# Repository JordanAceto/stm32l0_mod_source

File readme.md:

## Small STM32L0 based modulation source PCB

### Features:
- tiny pcb
- four analog inputs
- three digital input/outputs
- two analog outputs
- it can be configured for various modulation duties, such as
    - a dual LFO
    - a single ADSR
    - other things?
- drop it into various projects that need a small modulation source

### Status:

Task | Status |
---------|--------------|
Schematic capture | &#9745;
PCB layout | &#9745;
Test build | &#9745;
Safe to order boards| &#9745;

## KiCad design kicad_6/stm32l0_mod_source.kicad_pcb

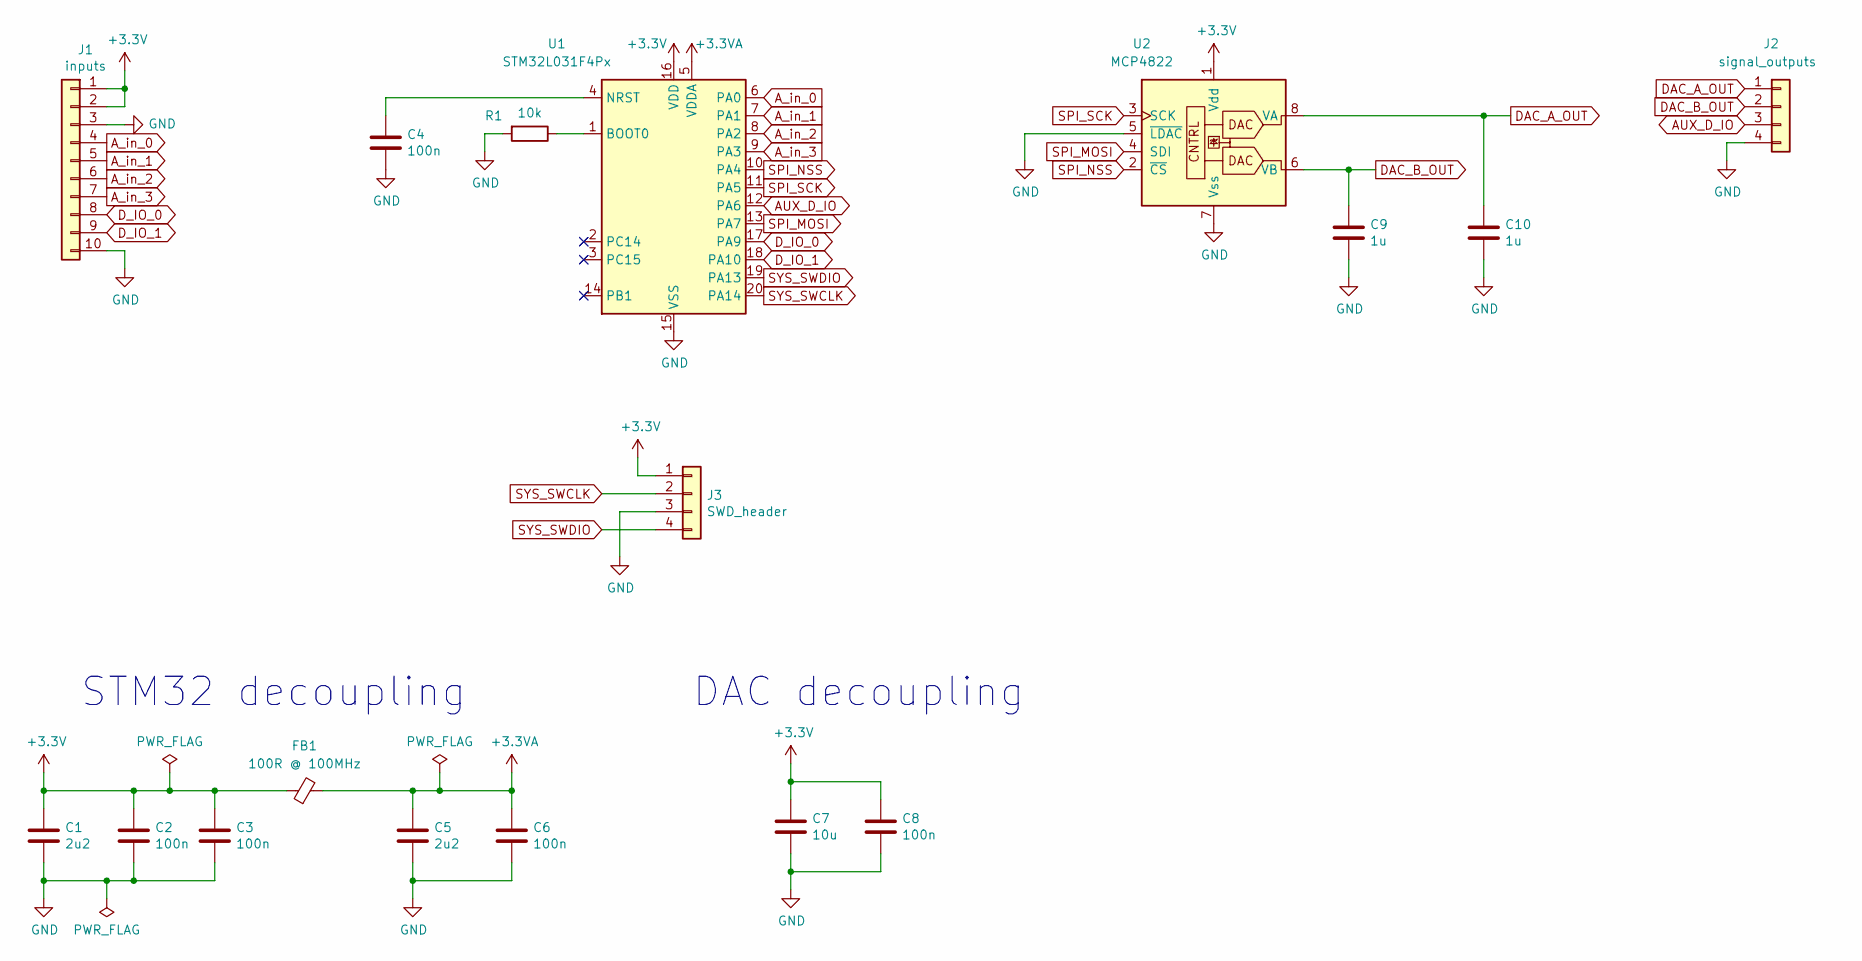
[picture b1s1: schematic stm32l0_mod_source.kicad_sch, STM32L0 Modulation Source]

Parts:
C1, C5: 2u2; C_0805_2012Metric
C2, C3, C4, C6, C8: 100n; C_0603_1608Metric
C7: 10u; C_0805_2012Metric
C9, C10: 1u; C_0805_2012Metric
FB1: 100R @ 100MHz; L_0805_2012Metric
J1: inputs; PinHeader_1x10_P2.54mm_Vertical
J2: signal_outputs; PinHeader_1x04_P2.54mm_Vertical
J3: SWD_header; PinHeader_1x04_P2.54mm_Vertical
R1: 10k; R_0603_1608Metric
U1: STM32L031F4Px; TSSOP-20_4.4x6.5mm_P0.65mm
U2: MCP4822; MSOP-8_3x3mm_P0.65mm

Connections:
+3.3V: C1.1, C2.1, C3.1, C7.1, C8.1, FB1.1, J1.1, J1.2, J3.1, U1.16 (VDD), U2.1 (Vdd)
+3.3VA: C5.1, C6.1, FB1.2, U1.5 (VDDA)
AUX_D_IO: J2.3, U1.12 (PA6)
A_in_0: J1.4, U1.6 (PA0)
A_in_1: J1.5, U1.7 (PA1)
A_in_2: J1.6, U1.8 (PA2)
A_in_3: J1.7, U1.9 (PA3)
DAC_A_OUT: C10.1, J2.1, U2.8 (VA)
DAC_B_OUT: C9.1, J2.2, U2.6 (VB)
D_IO_0: J1.8, U1.17 (PA9)
D_IO_1: J1.9, U1.18 (PA10)
GND: C1.2, C2.2, C3.2, C4.2, C5.2, C6.2, C7.2, C8.2, C9.2, C10.2, J1.3, J1.10, J2.4, J3.3, R1.2, U1.15 (VSS), U2.5 (~LDAC), U2.7 (Vss)
unnamed: C4.1, U1.4 (NRST)
unnamed: R1.1, U1.1 (BOOT0)
SPI_MOSI: U1.13 (PA7), U2.4 (SDI)
SPI_NSS: U1.10 (PA4), U2.2 (~CS)
SPI_SCK: U1.11 (PA5), U2.3 (SCK)
SYS_SWCLK: J3.2, U1.20 (PA14)
SYS_SWDIO: J3.4, U1.19 (PA13)

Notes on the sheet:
STM32 decoupling
DAC decoupling

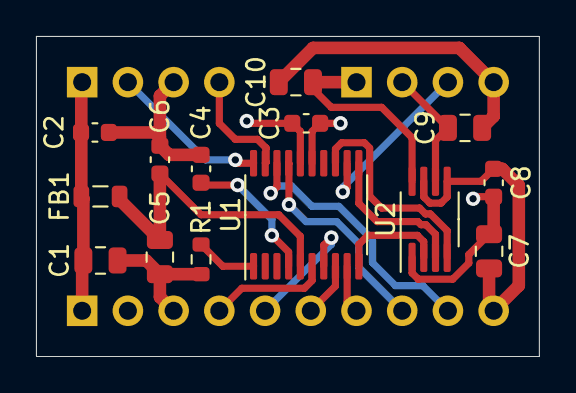
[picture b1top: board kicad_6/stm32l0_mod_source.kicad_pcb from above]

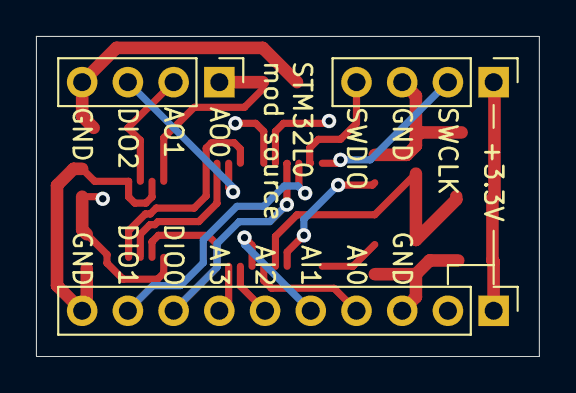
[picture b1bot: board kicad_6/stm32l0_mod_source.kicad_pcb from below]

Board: 4 copper layers, 27.9 x 17.8 mm, 17 parts (3 on the bottom side), 19 nets.

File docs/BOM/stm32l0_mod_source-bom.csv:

Row,Description,Part,References,Value,Footprint,Quantity Per PCB,Status,Datasheet
1,Unpolarized capacitor,C,C2 C3 C4 C6 C8,100n,C_0603_1608Metric,5, ,~
2,Unpolarized capacitor,C,C9 C10,1u,C_0805_2012Metric,2, ,~
3,Unpolarized capacitor,C,C1 C5,2u2,C_0805_2012Metric,2, ,~
4,Unpolarized capacitor,C,C7,10u,C_0805_2012Metric,1, ,~
5,"Ferrite bead, small symbol",FerriteBead_Small,FB1,100R @ 100MHz,L_0805_2012Metric,1, ,~
6,"Generic connector, single row, 01x10, script generated (kicad-library-utils/schlib/autogen/connector/)",Conn_01x10,J1,inputs,PinHeader_1x10_P2.54mm_Vertical,1, ,~
7,"Generic connector, single row, 01x04, script generated (kicad-library-utils/schlib/autogen/connector/)",Conn_01x04,J2 J3,signal_outputs,PinHeader_1x04_P2.54mm_Vertical,2, ,~
8,Resistor,R,R1,10k,R_0603_1608Metric,1, ,~
9,2-Channel 12-Bit D/A Converters with SPI Interface and Internal Reference (2.048V),MCP4822,U2,MCP4822,MSOP-8_3x3mm_P0.65mm,1, ,http://ww1.microchip.com/downloads/en/DeviceDoc/20002249B.pdf
10,"ARM Cortex-M0+ MCU, 16KB flash, 8KB RAM, 32MHz, 1.65-3.6V, 15 GPIO, TSSOP-20",STM32L031F4Px,U1,STM32L031F4Px,TSSOP-20_4.4x6.5mm_P0.65mm,1, ,http://www.st.com/st-web-ui/static/active/en/resource/techni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





Project info:
Schematic:,stm32l0_mod_source
Variant:,default
Revision:,0.1
Date:,2022-01-15
KiCad Version:,6.0.5+dfsg-1~bpo11+1
Statistics:
Component Groups:,10
Component Count:,17 (14 SMD/ 3 THT)
Fitted Components:,17 (14 SMD/ 3 THT)
Number of PCBs:,1
Total Components:,17

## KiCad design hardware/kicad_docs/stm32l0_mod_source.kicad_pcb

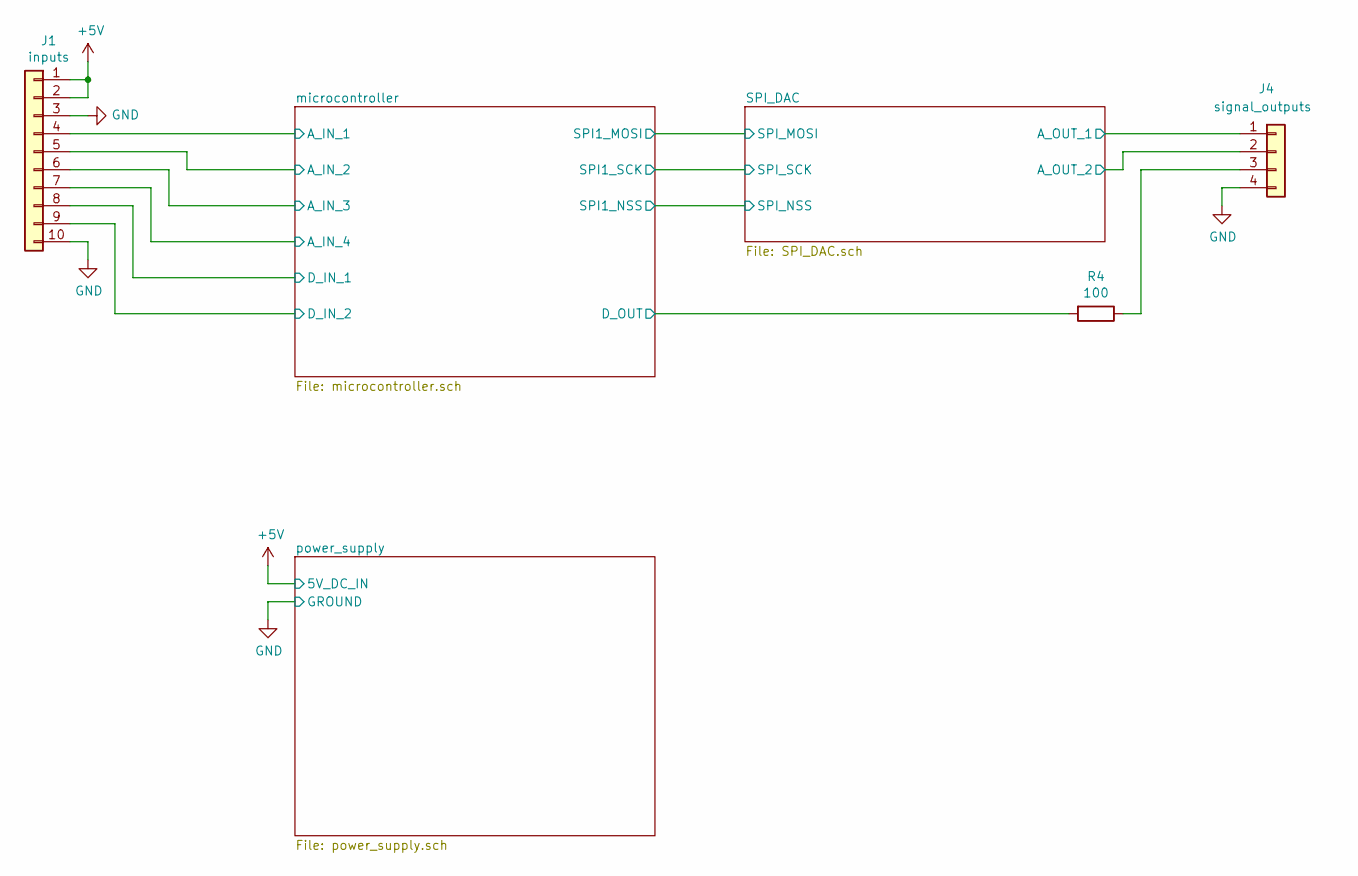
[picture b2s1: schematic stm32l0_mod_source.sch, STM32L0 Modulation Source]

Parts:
J1: inputs; PinHeader_1x10_P2.54mm_Vertical
J4: signal_outputs; PinHeader_1x04_P2.54mm_Vertical
R4: 100; R_0603_1608Metric

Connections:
+5V: J1.1, J1.2; also elsewhere on the board
/SPI_DAC_and_lowpass_filters/A_OUT_1: J4.1; also elsewhere on the board
/SPI_DAC_and_lowpass_filters/A_OUT_2: J4.2; also elsewhere on the board
/microcontroller/A_IN_1: J1.4; also elsewhere on the board
/microcontroller/A_IN_2: J1.5; also elsewhere on the board
/microcontroller/A_IN_3: J1.6; also elsewhere on the board
/microcontroller/A_IN_4: J1.7; also elsewhere on the board
/microcontroller/D_IN_1: J1.8; also elsewhere on the board
/microcontroller/D_IN_2: J1.9; also elsewhere on the board
/microcontroller/D_OUT: R4.2; also elsewhere on the board
GND: J1.3, J1.10, J4.4; also elsewhere on the board
unnamed: J4.3, R4.1

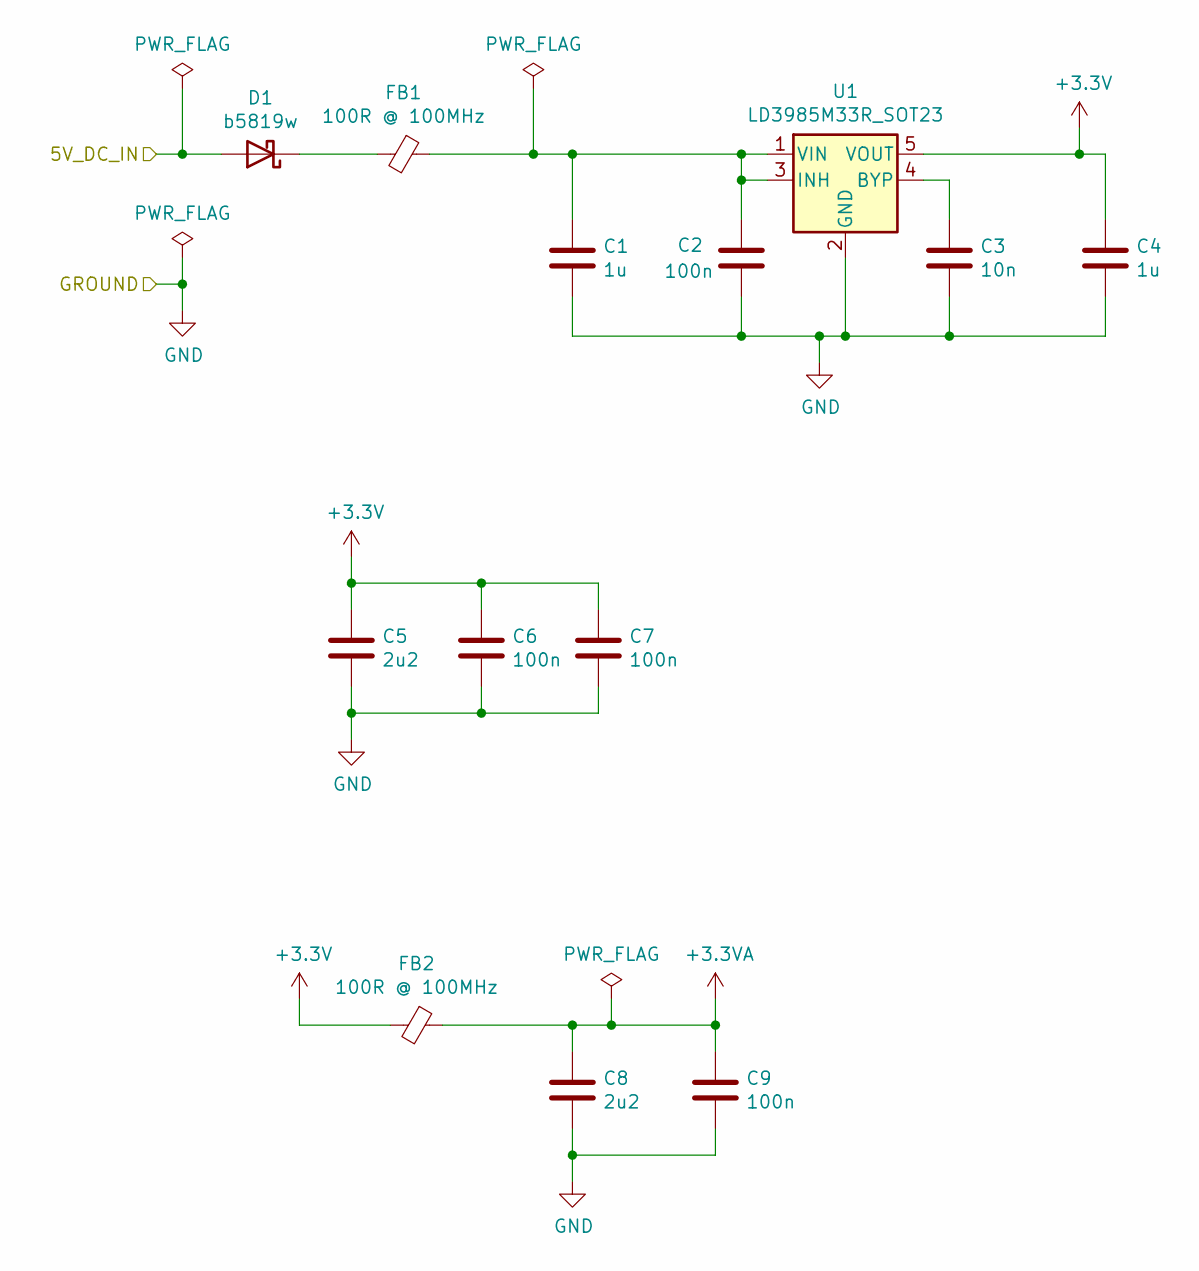
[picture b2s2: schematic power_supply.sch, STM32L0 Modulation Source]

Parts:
C1, C4: 1u; C_0805_2012Metric
C2, C6, C7, C9: 100n; C_0603_1608Metric
C3: 10n; C_0603_1608Metric
C5, C8: 2u2; C_0805_2012Metric
D1: b5819w; D_SOD-323
FB1, FB2: 100R @ 100MHz; L_0805_2012Metric
U1: LD3985M33R_SOT23; SOT-23-5

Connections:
+3.3VA: C8.1, C9.1, FB2.1; also elsewhere on the board
+3V3: C4.1, C5.1, C6.1, C7.1, FB2.2, U1.5 (VOUT); also elsewhere on the board
+5V: D1.2 (A); also elsewhere on the board
GND: C1.2, C2.2, C3.2, C4.2, C5.2, C6.2, C7.2, C8.2, C9.2, U1.2 (GND); also elsewhere on the board
unnamed: C1.1, C2.1, FB1.1, U1.1 (VIN), U1.3 (INH)
unnamed: C3.1, U1.4 (BYP)
unnamed: D1.1 (K), FB1.2

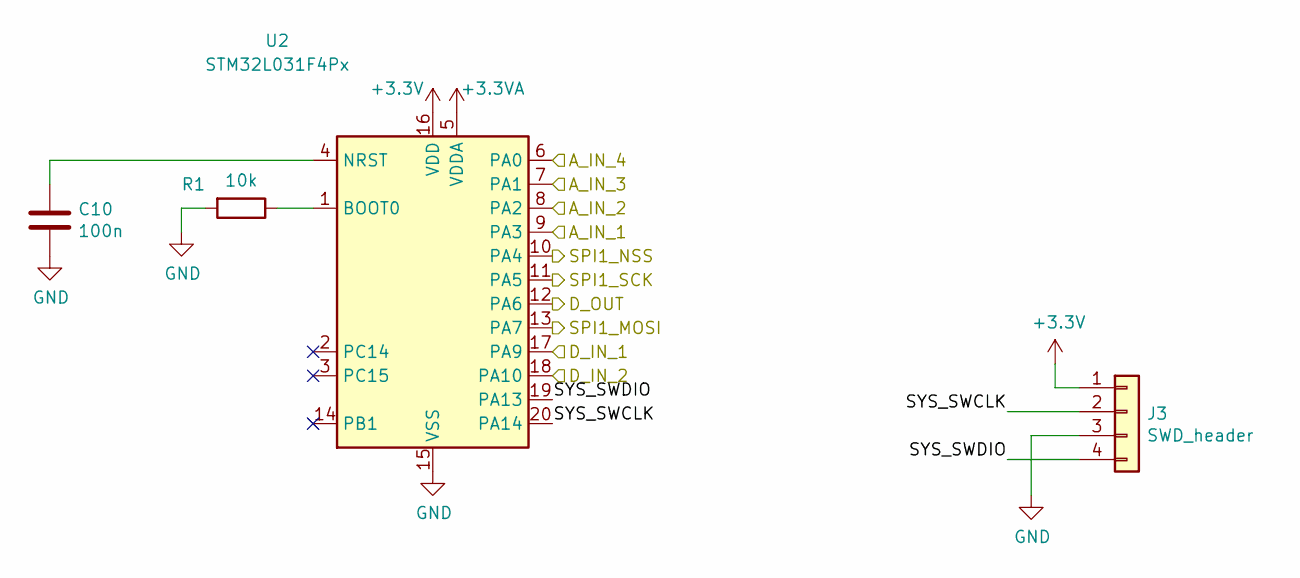
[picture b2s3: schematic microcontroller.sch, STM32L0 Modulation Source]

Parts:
C10: 100n; C_0603_1608Metric
J3: SWD_header; PinHeader_1x04_P2.54mm_Vertical
R1: 10k; R_0603_1608Metric
U2: STM32L031F4Px; TSSOP-20_4.4x6.5mm_P0.65mm

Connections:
+3.3VA: U2.5 (VDDA); also elsewhere on the board
+3V3: J3.1, U2.16 (VDD); also elsewhere on the board
/microcontroller/A_IN_1: U2.9 (PA3); also elsewhere on the board
/microcontroller/A_IN_2: U2.8 (PA2); also elsewhere on the board
/microcontroller/A_IN_3: U2.7 (PA1); also elsewhere on the board
/microcontroller/A_IN_4: U2.6 (PA0); also elsewhere on the board
/microcontroller/D_IN_1: U2.17 (PA9); also elsewhere on the board
/microcontroller/D_IN_2: U2.18 (PA10); also elsewhere on the board
/microcontroller/D_OUT: U2.12 (PA6); also elsewhere on the board
/microcontroller/SPI1_MOSI: U2.13 (PA7); also elsewhere on the board
/microcontroller/SPI1_NSS: U2.10 (PA4); also elsewhere on the board
/microcontroller/SPI1_SCK: U2.11 (PA5); also elsewhere on the board
/microcontroller/SYS_SWCLK: J3.2, U2.20 (PA14)
/microcontroller/SYS_SWDIO: J3.4, U2.19 (PA13)
GND: C10.2, J3.3, R1.2, U2.15 (VSS); also elsewhere on the board
unnamed: C10.1, U2.4 (NRST)
unnamed: R1.1, U2.1 (BOOT0)

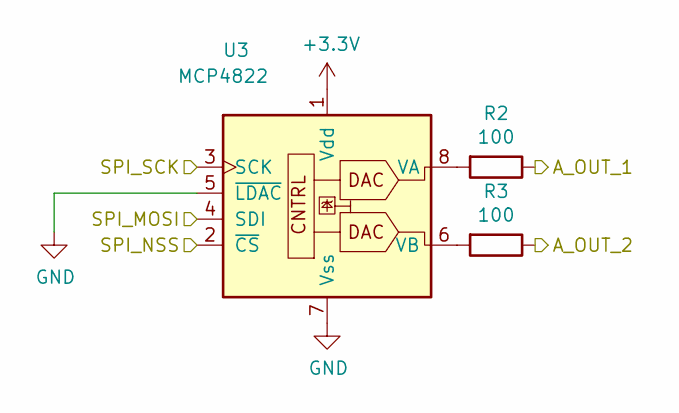
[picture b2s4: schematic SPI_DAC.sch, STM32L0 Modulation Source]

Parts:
R2, R3: 100; R_0603_1608Metric
U3: MCP4822; MSOP-8_3x3mm_P0.65mm

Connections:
+3V3: U3.1 (Vdd); also elsewhere on the board
/SPI_DAC_and_lowpass_filters/A_OUT_1: R2.1; also elsewhere on the board
/SPI_DAC_and_lowpass_filters/A_OUT_2: R3.1; also elsewhere on the board
/microcontroller/SPI1_MOSI: U3.4 (SDI); also elsewhere on the board
/microcontroller/SPI1_NSS: U3.2 (~CS); also elsewhere on the board
/microcontroller/SPI1_SCK: U3.3 (SCK); also elsewhere on the board
GND: U3.5 (~LDAC), U3.7 (Vss); also elsewhere on the board
unnamed: R2.2, U3.8 (VA)
unnamed: R3.2, U3.6 (VB)

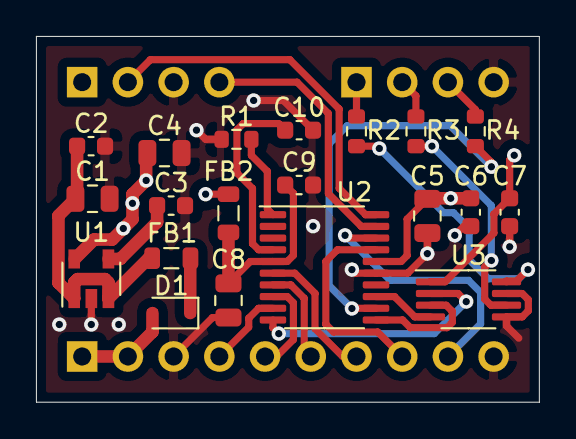
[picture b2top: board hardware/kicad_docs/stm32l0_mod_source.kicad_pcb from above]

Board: 4 copper layers, 27.9 x 20.3 mm, 23 parts (0 on the bottom side), 26 nets.

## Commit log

2021-06-12 add some datasheets
2021-06-12 refine pcb
2021-06-12 add interactivce BOM
2021-06-12 add pdf schematic
2021-06-12 add some rendered pics
2021-06-12 add gerbers
2021-06-13 fix typo in name
2022-12-28 Shrink board, new layout
2022-12-28 Add license text
2024-04-28 Update gitignore for incoming example project
2024-04-28 Add STM32CubeIDE basic example to exercise and verify the board
2024-04-28 Add README and images to explain the CubeIDE example project
2024-04-28 Fix several typos in example README

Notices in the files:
hardware/kicad_docs/SPI_DAC.sch:
creativecommons.org/licences/by/4.0
Licence: CC by 4.0
kicad_6/stm32l0_mod_source.kicad_pcb:
creativecommons.org/licenses/by/4.0
License: CC by 4.0
